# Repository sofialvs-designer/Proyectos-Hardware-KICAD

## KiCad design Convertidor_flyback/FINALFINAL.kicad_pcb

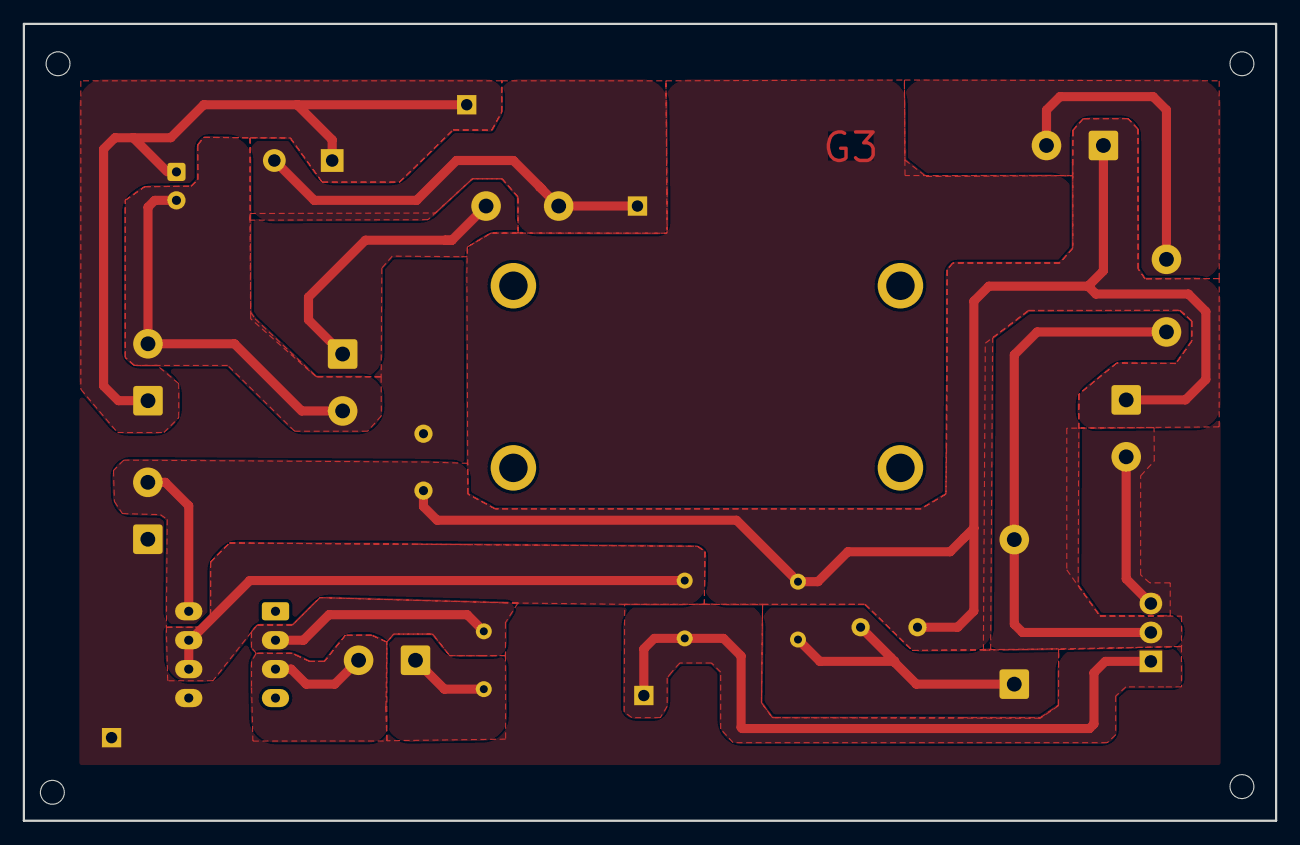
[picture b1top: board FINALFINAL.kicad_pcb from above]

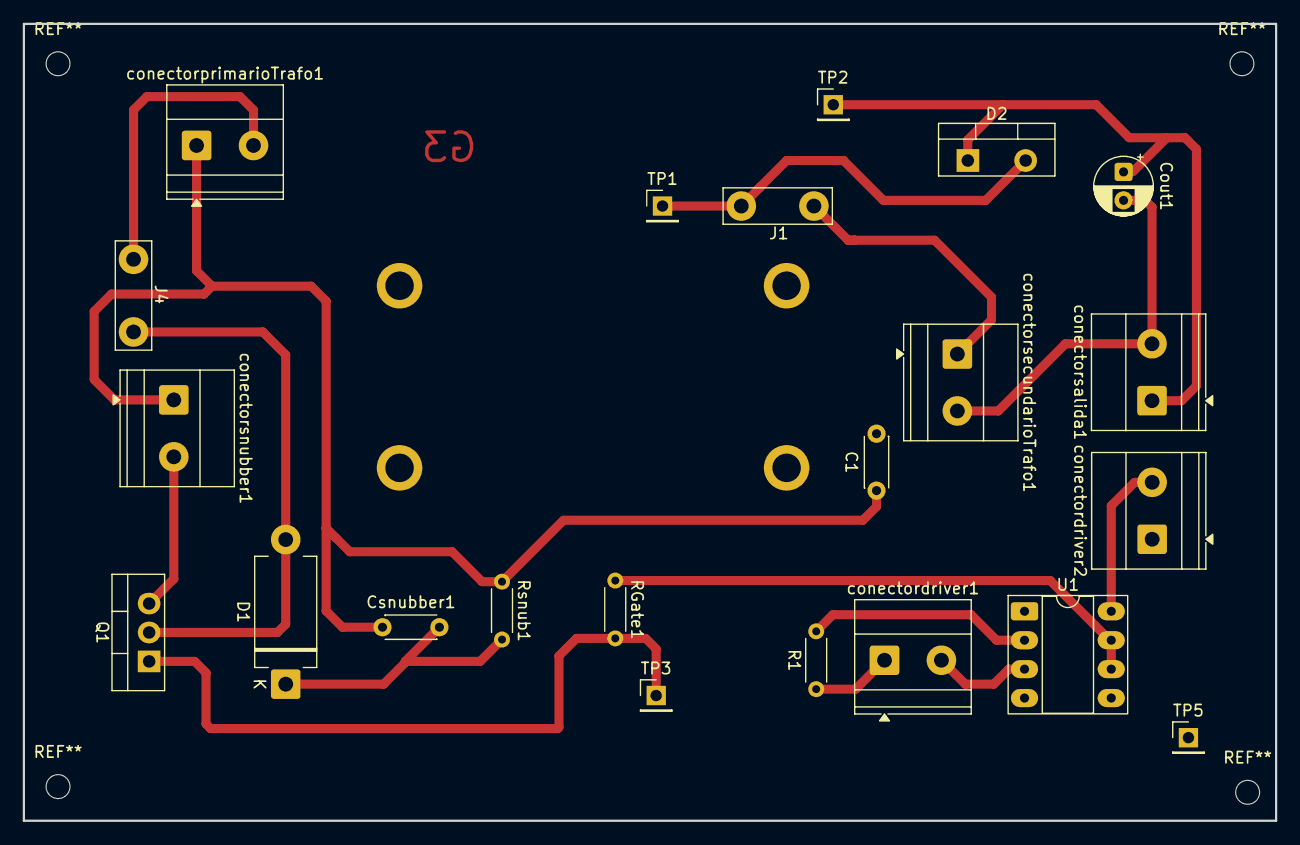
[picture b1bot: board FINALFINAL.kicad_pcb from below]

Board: 2 copper layers, 110.0 x 70.0 mm, 23 parts (23 on the bottom side), 14 nets.

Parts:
C1: 100nF; C_Disc_D4.3mm_W1.9mm_P5.00mm
Cout1: 2.2uF; CP_Radial_D5.0mm_P2.50mm
Csnubber1: 4.7 nF; C_Disc_D4.3mm_W1.9mm_P5.00mm
D1: D; D_DO-201_P12.70mm_Horizontal
D2: C3D10060A; TO-220-2_Vertical
J1, J4: Conn_01x02; TestPoint_Bridge_Pitch6.35mm_Drill1.3mm
Q1: IRF540N; TO-220-3_Vertical
R1: 270; R_Axial_DIN0204_L3.6mm_D1.6mm_P5.08mm_Horizontal
RGate1: 8; R_Axial_DIN0204_L3.6mm_D1.6mm_P5.08mm_Horizontal
Rsnub1: 33; R_Axial_DIN0204_L3.6mm_D1.6mm_P5.08mm_Horizontal
T1: Transformer_1P_1S; trafoxd
TP1, TP2, TP3, TP5: TestPoint; PinHeader_1x01_P2.54mm_Vertical
U1: HCPL-3120; DIP-8_W7.62mm_Socket_LongPads
conectordriver1, conectordriver2: Screw_Terminal_01x02; TerminalBlock_Phoenix_MKDS-1,5-2_1x02_P5.00mm_Horizontal
conectorprimarioTrafo1: Screw_Terminal_01x02; TerminalBlock_Phoenix_MKDS-1,5-2_1x02_P5.00mm_Horizontal
conectorsalida1: Screw_Terminal_01x02; TerminalBlock_Phoenix_MKDS-1,5-2_1x02_P5.00mm_Horizontal
conectorsecundarioTrafo1: Screw_Terminal_01x02; TerminalBlock_Phoenix_MKDS-1,5-2_1x02_P5.00mm_Horizontal
conectorsnubber1: Screw_Terminal_01x02; TerminalBlock_Phoenix_MKDS-1,5-2_1x02_P5.00mm_Horizontal

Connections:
GND: Cout1.2, T1.3 (SA), conectorsalida1.2, conectorsecundarioTrafo1.2
GNDD: U1.3 (C), conectordriver1.2
unnamed: D1.2 (A), J4.1, Q1.2 (D)
unnamed: Csnubber1.2, D1.1 (K), Rsnub1.2
unnamed: D2.2 (A), J1.2, TP1.1
unnamed: Cout1.1, D2.1 (K), TP2.1, conectorsalida1.1
unnamed: J1.1, conectorsecundarioTrafo1.1
unnamed: J4.2, conectorprimarioTrafo1.2
unnamed: Q1.1 (G), RGate1.2, TP3.1
unnamed: RGate1.1, U1.6 (VO), U1.7 (VO)
unnamed: C1.1, Csnubber1.1, Rsnub1.1, T1.1 (AA), U1.8 (VCC), conectordriver2.2, conectorprimarioTrafo1.1, conectorsnubber1.1
unnamed: R1.2, U1.2 (A)
unnamed: R1.1, conectordriver1.1
PGND: C1.2, Q1.3 (S), TP5.1, U1.5 (VEE), conectordriver2.1, conectorsnubber1.2

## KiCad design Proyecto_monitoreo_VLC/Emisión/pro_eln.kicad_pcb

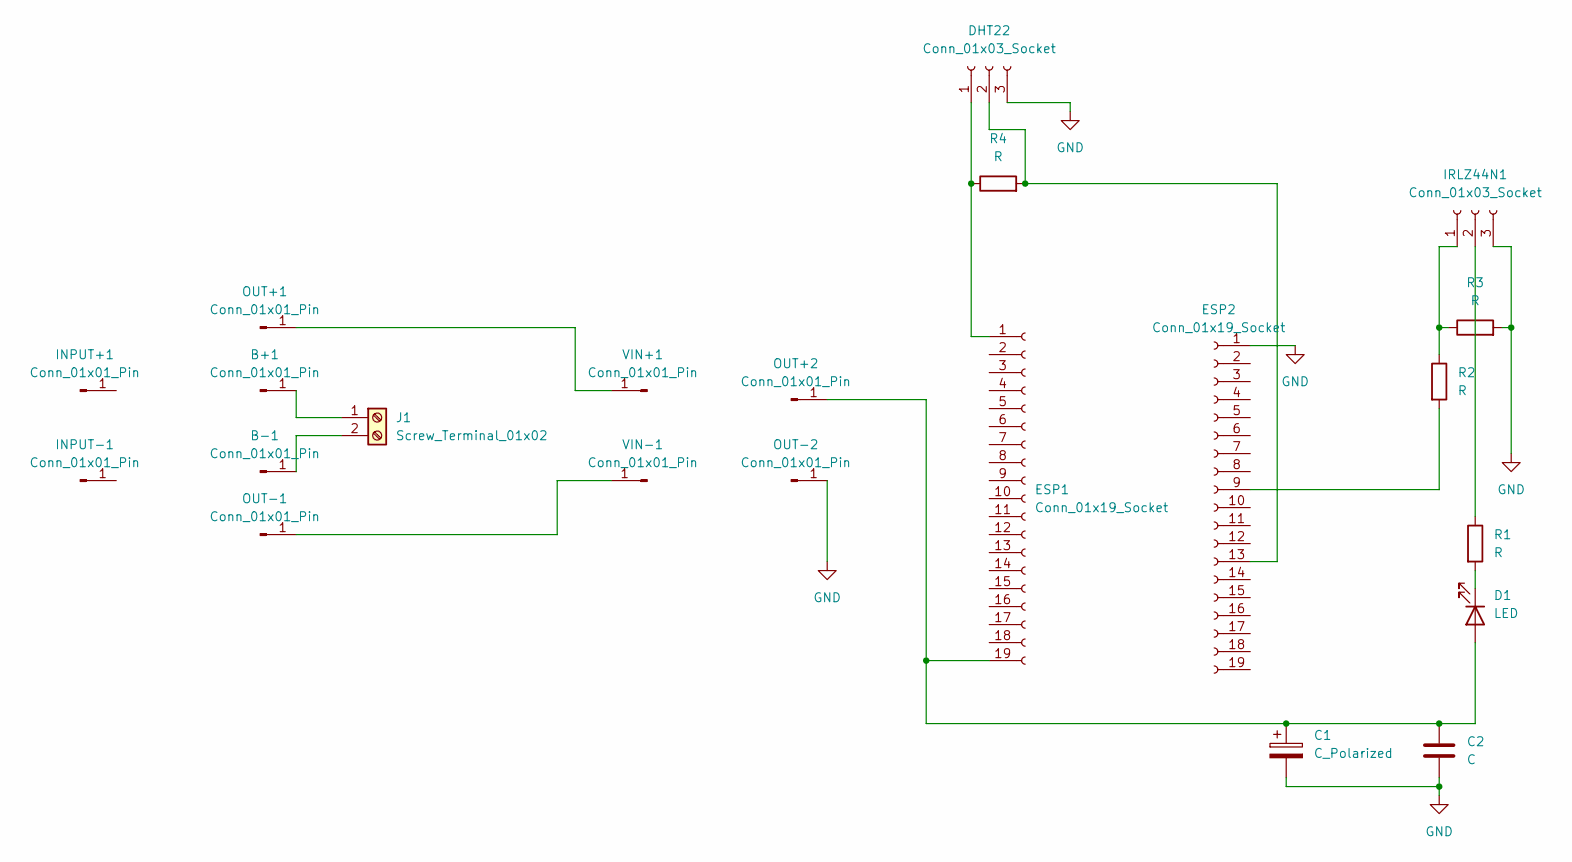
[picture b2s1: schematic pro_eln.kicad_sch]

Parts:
B+1: Conn_01x01_Pin; PinSocket_1x01_P2.54mm_Vertical
B-1: Conn_01x01_Pin; PinSocket_1x01_P2.54mm_Vertical
C1: C_Polarized; CP_Radial_D5.0mm_P2.50mm
C2: C; C_Disc_D4.3mm_W1.9mm_P5.00mm
D1: LED; TerminalBlock_Phoenix_MKDS-1,5-2-5.08_1x02_P5.08mm_Horizont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
DHT22: Conn_01x03_Socket; PinSocket_1x03_P2.54mm_Vertical
ESP1, ESP2: Conn_01x19_Socket; PinSocket_1x19_P2.54mm_Vertical
INPUT+1: Conn_01x01_Pin; PinSocket_1x01_P2.54mm_Vertical
INPUT-1: Conn_01x01_Pin; PinSocket_1x01_P2.54mm_Vertical
IRLZ44N1: Conn_01x03_Socket; PinSocket_1x03_P2.54mm_Vertical
J1: Screw_Terminal_01x02; TerminalBlock_Phoenix_MKDS-1,5-2-5.08_1x02_P5.08mm_Horizont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
OUT+1, OUT+2: Conn_01x01_Pin; PinSocket_1x01_P2.54mm_Vertical
OUT-1, OUT-2: Conn_01x01_Pin; PinSocket_1x01_P2.54mm_Vertical
R1: R; R_Axial_DIN0207_L6.3mm_D2.5mm_P15.24mm_Horizontal
R2, R3, R4: R; R_Axial_DIN0207_L6.3mm_D2.5mm_P10.16mm_Horizontal
VIN+1: Conn_01x01_Pin; PinSocket_1x01_P2.54mm_Vertical
VIN-1: Conn_01x01_Pin; PinSocket_1x01_P2.54mm_Vertical

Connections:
GND: C1.2, C2.2, DHT22.3, ESP2.1, IRLZ44N1.3, OUT-2.1 (Pin_1_1), R3.2
unnamed: B+1.1 (Pin_1_1), J1.1
unnamed: B-1.1 (Pin_1_1), J1.2
unnamed: C1.1, C2.1, D1.2 (A), ESP1.19, OUT+2.1 (Pin_1_1)
unnamed: D1.1 (K), R1.2
unnamed: DHT22.1, ESP1.1, R4.1
unnamed: DHT22.2, ESP2.13, R4.2
unnamed: ESP2.9, R2.2
unnamed: IRLZ44N1.1, R2.1, R3.1
unnamed: IRLZ44N1.2, R1.1
unnamed: OUT+1.1 (Pin_1_1), VIN+1.1 (Pin_1_1)
unnamed: OUT-1.1 (Pin_1_1), VIN-1.1 (Pin_1_1)

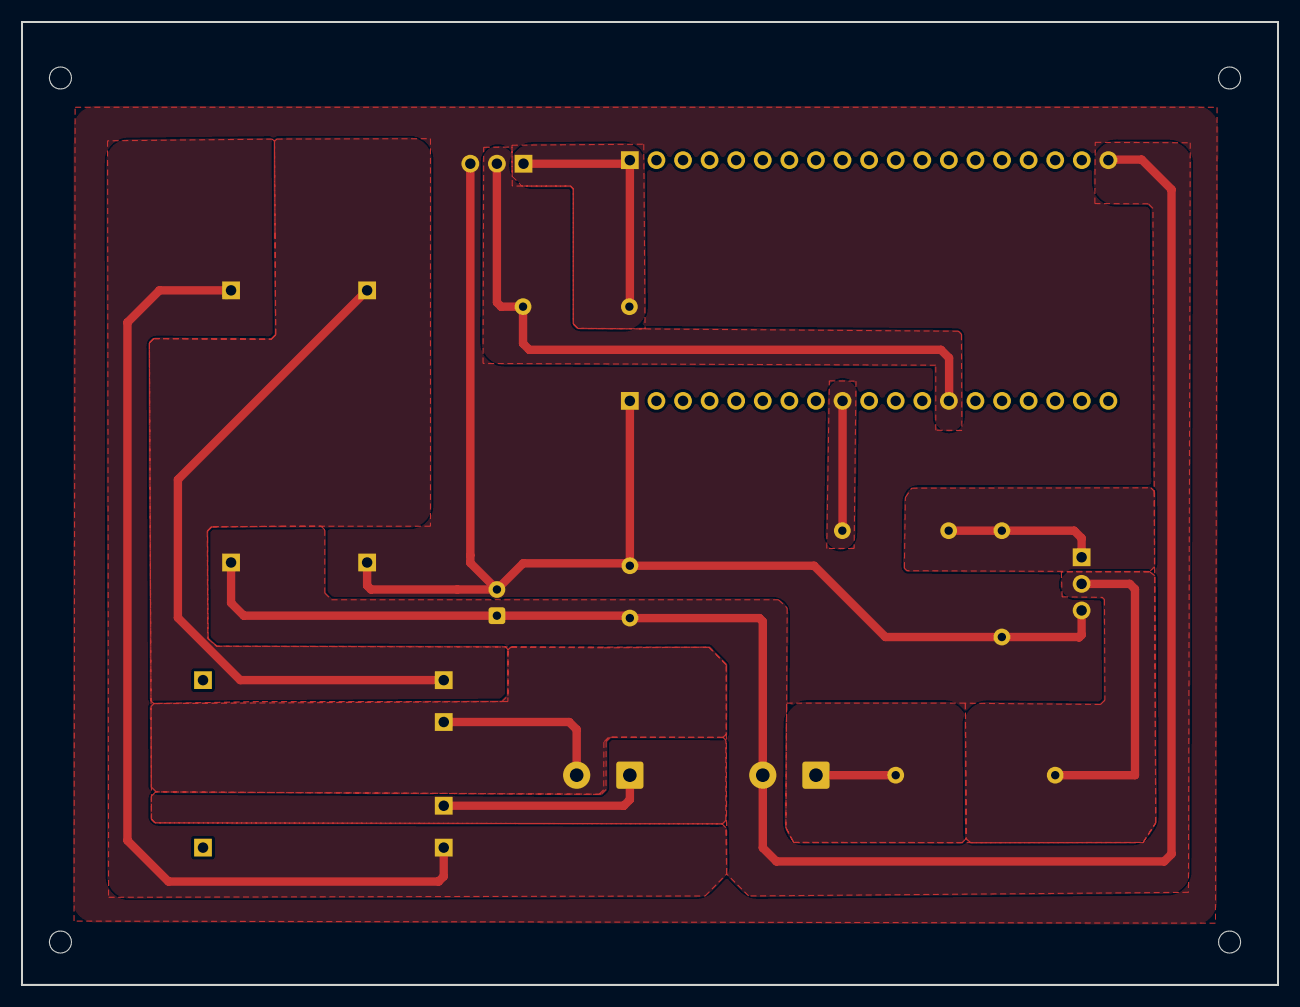
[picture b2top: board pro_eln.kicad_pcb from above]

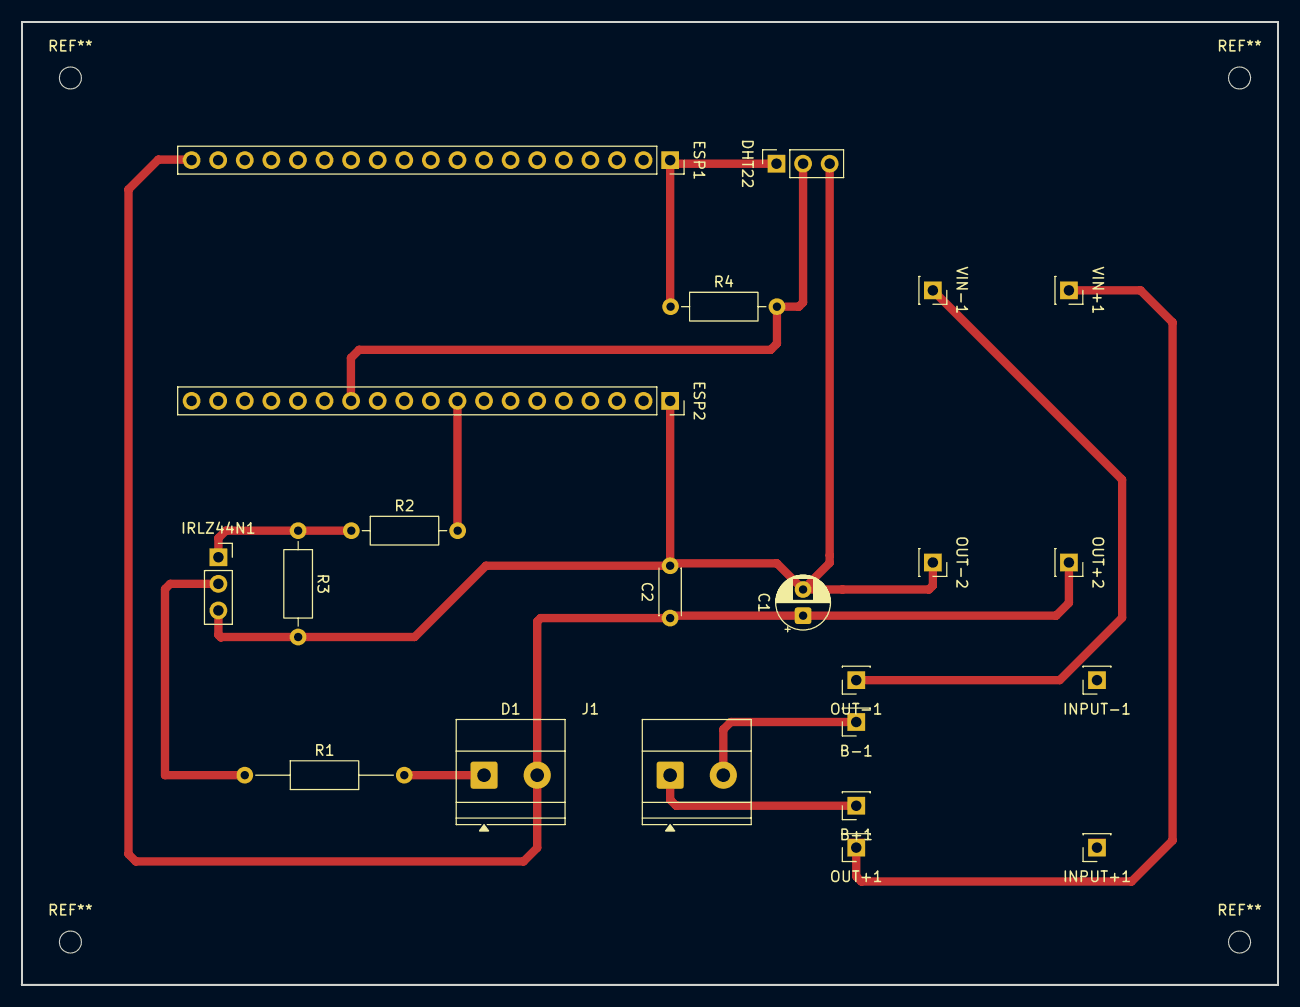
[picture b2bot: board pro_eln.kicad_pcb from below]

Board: 2 copper layers, 120.0 x 92.0 mm, 22 parts (22 on the bottom side), 12 nets.

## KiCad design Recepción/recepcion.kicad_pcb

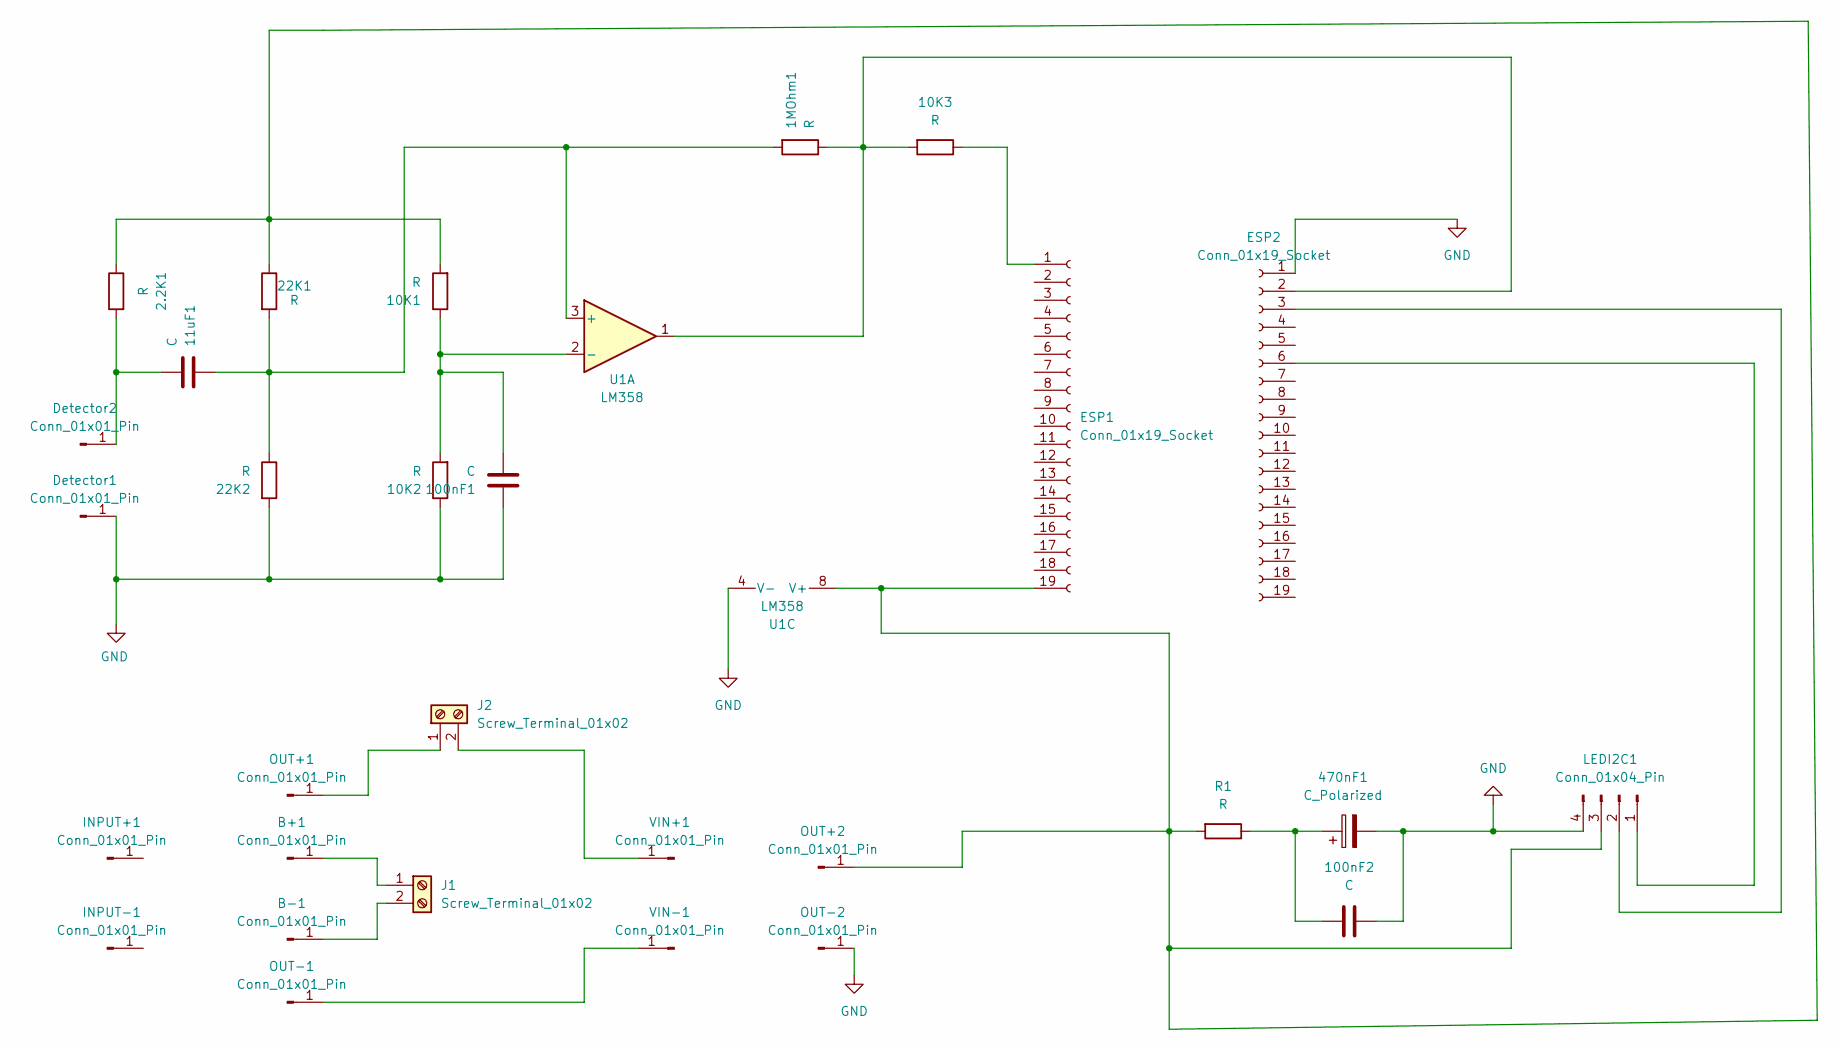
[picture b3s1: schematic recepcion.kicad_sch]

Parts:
1MOhm1, 2.2K1, 10K1, 10K2, 10K3, 22K1, 22K2: R; R_Axial_DIN0207_L6.3mm_D2.5mm_P10.16mm_Horizontal
11uF1: C; TerminalBlock_Phoenix_MKDS-1,5-2-5.08_1x02_P5.08mm_Horizont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
100nF1, 100nF2: C; C_Radial_D5.0mm_H5.0mm_P2.00mm
470nF1: C_Polarized; C_Radial_D5.0mm_H5.0mm_P2.00mm
B+1: Conn_01x01_Pin; PinSocket_1x01_P2.54mm_Vertical
B-1: Conn_01x01_Pin; PinSocket_1x01_P2.54mm_Vertical
Detector1, Detector2: Conn_01x01_Pin; PinSocket_1x01_P2.54mm_Vertical
ESP1, ESP2: Conn_01x19_Socket; PinSocket_1x19_P2.54mm_Vertical
INPUT+1: Conn_01x01_Pin; PinSocket_1x01_P2.54mm_Vertical
INPUT-1: Conn_01x01_Pin; PinSocket_1x01_P2.54mm_Vertical
J1, J2: Screw_Terminal_01x02; TerminalBlock_Phoenix_MKDS-1,5-2-5.08_1x02_P5.08mm_Horizont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
LEDI2C1: Conn_01x04_Pin; PinSocket_1x04_P2.54mm_Vertical
OUT+1, OUT+2: Conn_01x01_Pin; PinSocket_1x01_P2.54mm_Vertical
OUT-1, OUT-2: Conn_01x01_Pin; PinSocket_1x01_P2.54mm_Vertical
R1: R; R_Axial_DIN0207_L6.3mm_D2.5mm_P15.24mm_Horizontal
U1: LM358; DIP-8_W7.62mm
VIN+1: Conn_01x01_Pin; PinSocket_1x01_P2.54mm_Vertical
VIN-1: Conn_01x01_Pin; PinSocket_1x01_P2.54mm_Vertical

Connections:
GND: 10K2.1, 22K2.2, 100nF1.1, 100nF2.1, 470nF1.2, Detector1.1 (Pin_1_1), ESP2.1, LEDI2C1.4, OUT-2.1 (Pin_1_1), U1.4 (V-)
unnamed: 100nF2.2, 470nF1.1, R1.1
unnamed: B+1.1 (Pin_1_1), J1.1
unnamed: B-1.1 (Pin_1_1), J1.2
unnamed: 2.2K1.2, 11uF1.1, Detector2.1 (Pin_1_1)
unnamed: 10K3.1, ESP1.1
unnamed: 2.2K1.1, 10K1.2, 22K1.1, ESP1.19, LEDI2C1.3, OUT+2.1 (Pin_1_1), R1.2, U1.8 (V+)
unnamed: 1MOhm1.1, 10K3.2, ESP2.2, U1.1
unnamed: ESP2.3, LEDI2C1.2
unnamed: ESP2.6, LEDI2C1.1
unnamed: J2.1, OUT+1.1 (Pin_1_1)
unnamed: J2.2, VIN+1.1 (Pin_1_1)
unnamed: OUT-1.1 (Pin_1_1), VIN-1.1 (Pin_1_1)
unnamed: 1MOhm1.2, 11uF1.2, 22K1.2, 22K2.1, U1.3 (+)
unnamed: 10K1.1, 10K2.2, 100nF1.2, U1.2 (-)

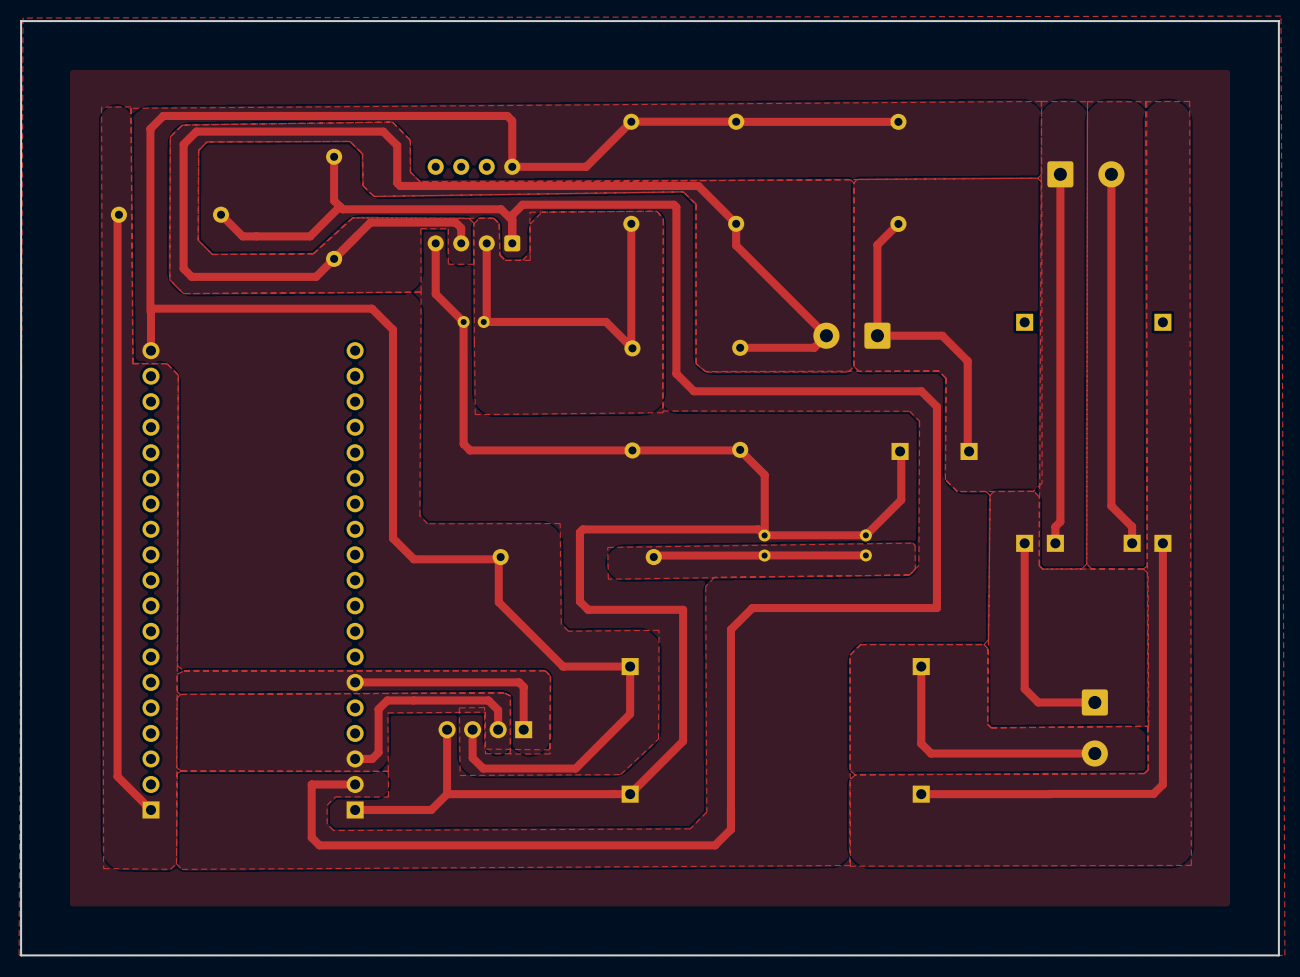
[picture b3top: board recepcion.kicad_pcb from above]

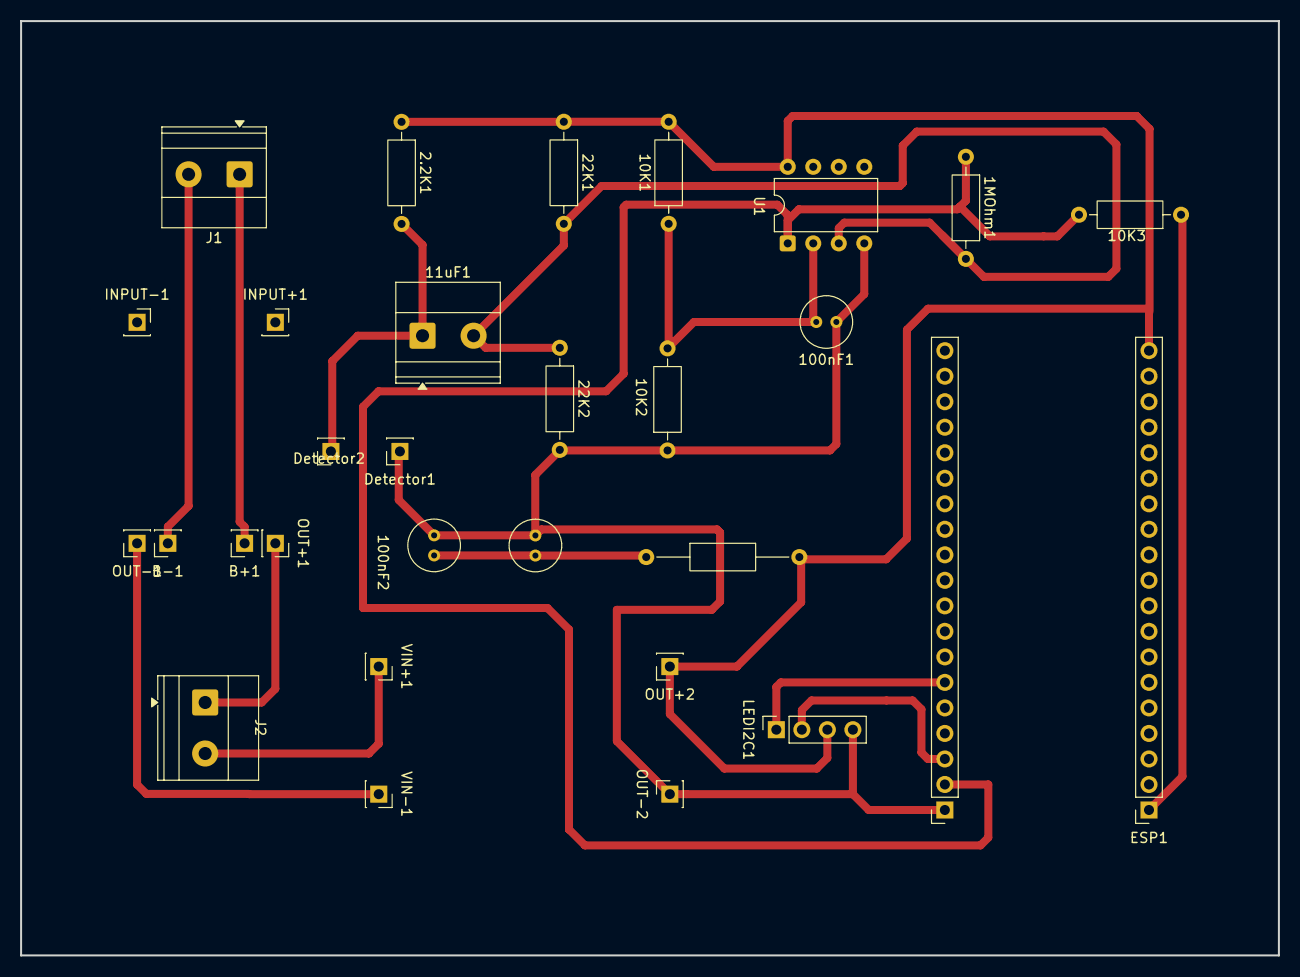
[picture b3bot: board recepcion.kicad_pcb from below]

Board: 2 copper layers, 125.2 x 93.0 mm, 30 parts (30 on the bottom side), 15 nets.
